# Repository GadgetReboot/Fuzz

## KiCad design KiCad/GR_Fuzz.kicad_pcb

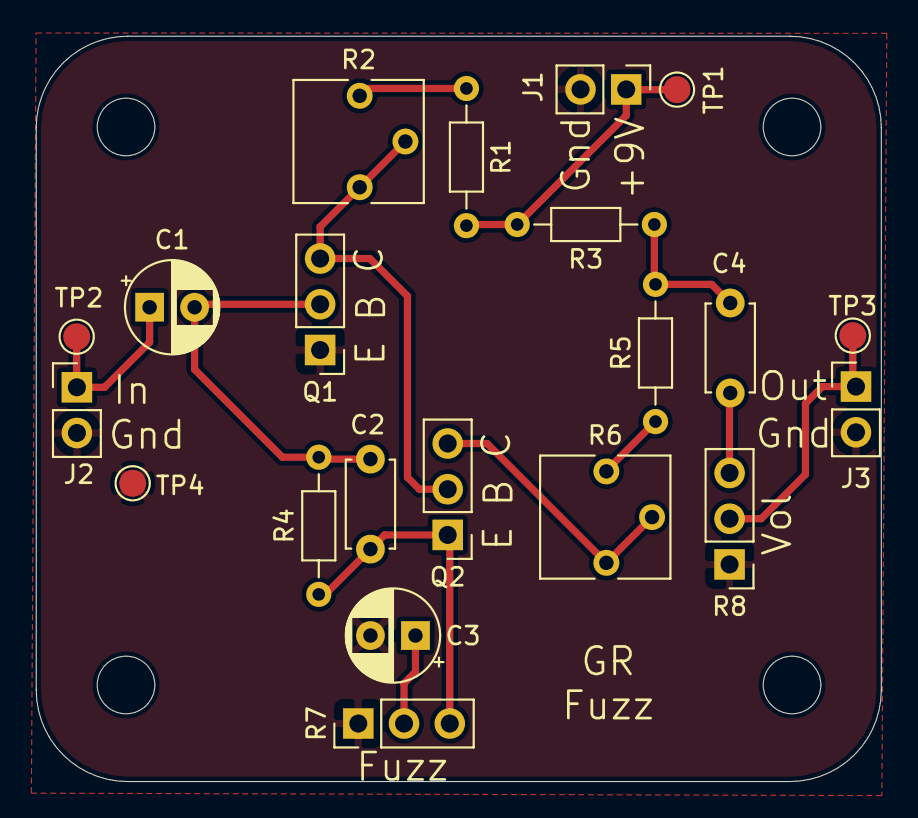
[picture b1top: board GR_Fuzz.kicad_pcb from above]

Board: 2 copper layers, 46.9 x 41.4 mm, 25 parts (0 on the bottom side), 13 nets.

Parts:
C1: 2u2; CP_Radial_D5.0mm_P2.50mm
C2: 470pF; C_Disc_D4.7mm_W2.5mm_P5.00mm
C3: 22u; CP_Radial_D5.0mm_P2.50mm
C4: 100nF; C_Disc_D4.7mm_W2.5mm_P5.00mm
J1, J2, J3: Conn_01x02; PinHeader_1x02_P2.54mm_Vertical
MH1, MH2, MH3, MH4: MountingHole; MountingHole_3.2mm_M3
Q1, Q2: 2N3904; PinHeader_1x03_P2.54mm_Vertical
R1: 20K; R_Axial_DIN0204_L3.6mm_D1.6mm_P7.62mm_Horizontal
R2: 50K; Potentiometer_Vishay_T73YP_Vertical
R3: 330r; R_Axial_DIN0204_L3.6mm_D1.6mm_P7.62mm_Horizontal
R4: 100K; R_Axial_DIN0204_L3.6mm_D1.6mm_P7.62mm_Horizontal
R5: 4K7; R_Axial_DIN0204_L3.6mm_D1.6mm_P7.62mm_Horizontal
R6: 10K; Potentiometer_Vishay_T73YP_Vertical
R7: 1K; PinHeader_1x03_P2.54mm_Vertical
R8: 500K; PinHeader_1x03_P2.54mm_Vertical
TP1, TP2, TP3, TP4: TestPoint; TestPoint_Pad_D1.5mm

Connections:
+9V: J1.1, R1.2, R3.2, TP1.1
/In: C1.1, J2.1, TP2.1
/Out: J3.1, R8.2, TP3.1
GNDREF: C3.2, J1.2, J2.2, J3.2, Q1.1, R7.1, R8.1, TP4.1
unnamed: C1.2, C2.2, Q1.2, R4.2
unnamed: C2.1, Q2.1, R4.1, R7.3
unnamed: C3.1, R7.2
unnamed: C4.1, R8.3
unnamed: C4.2, R3.1, R5.2
unnamed: Q1.3, Q2.2, R2.1, R2.2
unnamed: Q2.3, R6.1, R6.2
unnamed: R1.1, R2.3
unnamed: R5.1, R6.3
